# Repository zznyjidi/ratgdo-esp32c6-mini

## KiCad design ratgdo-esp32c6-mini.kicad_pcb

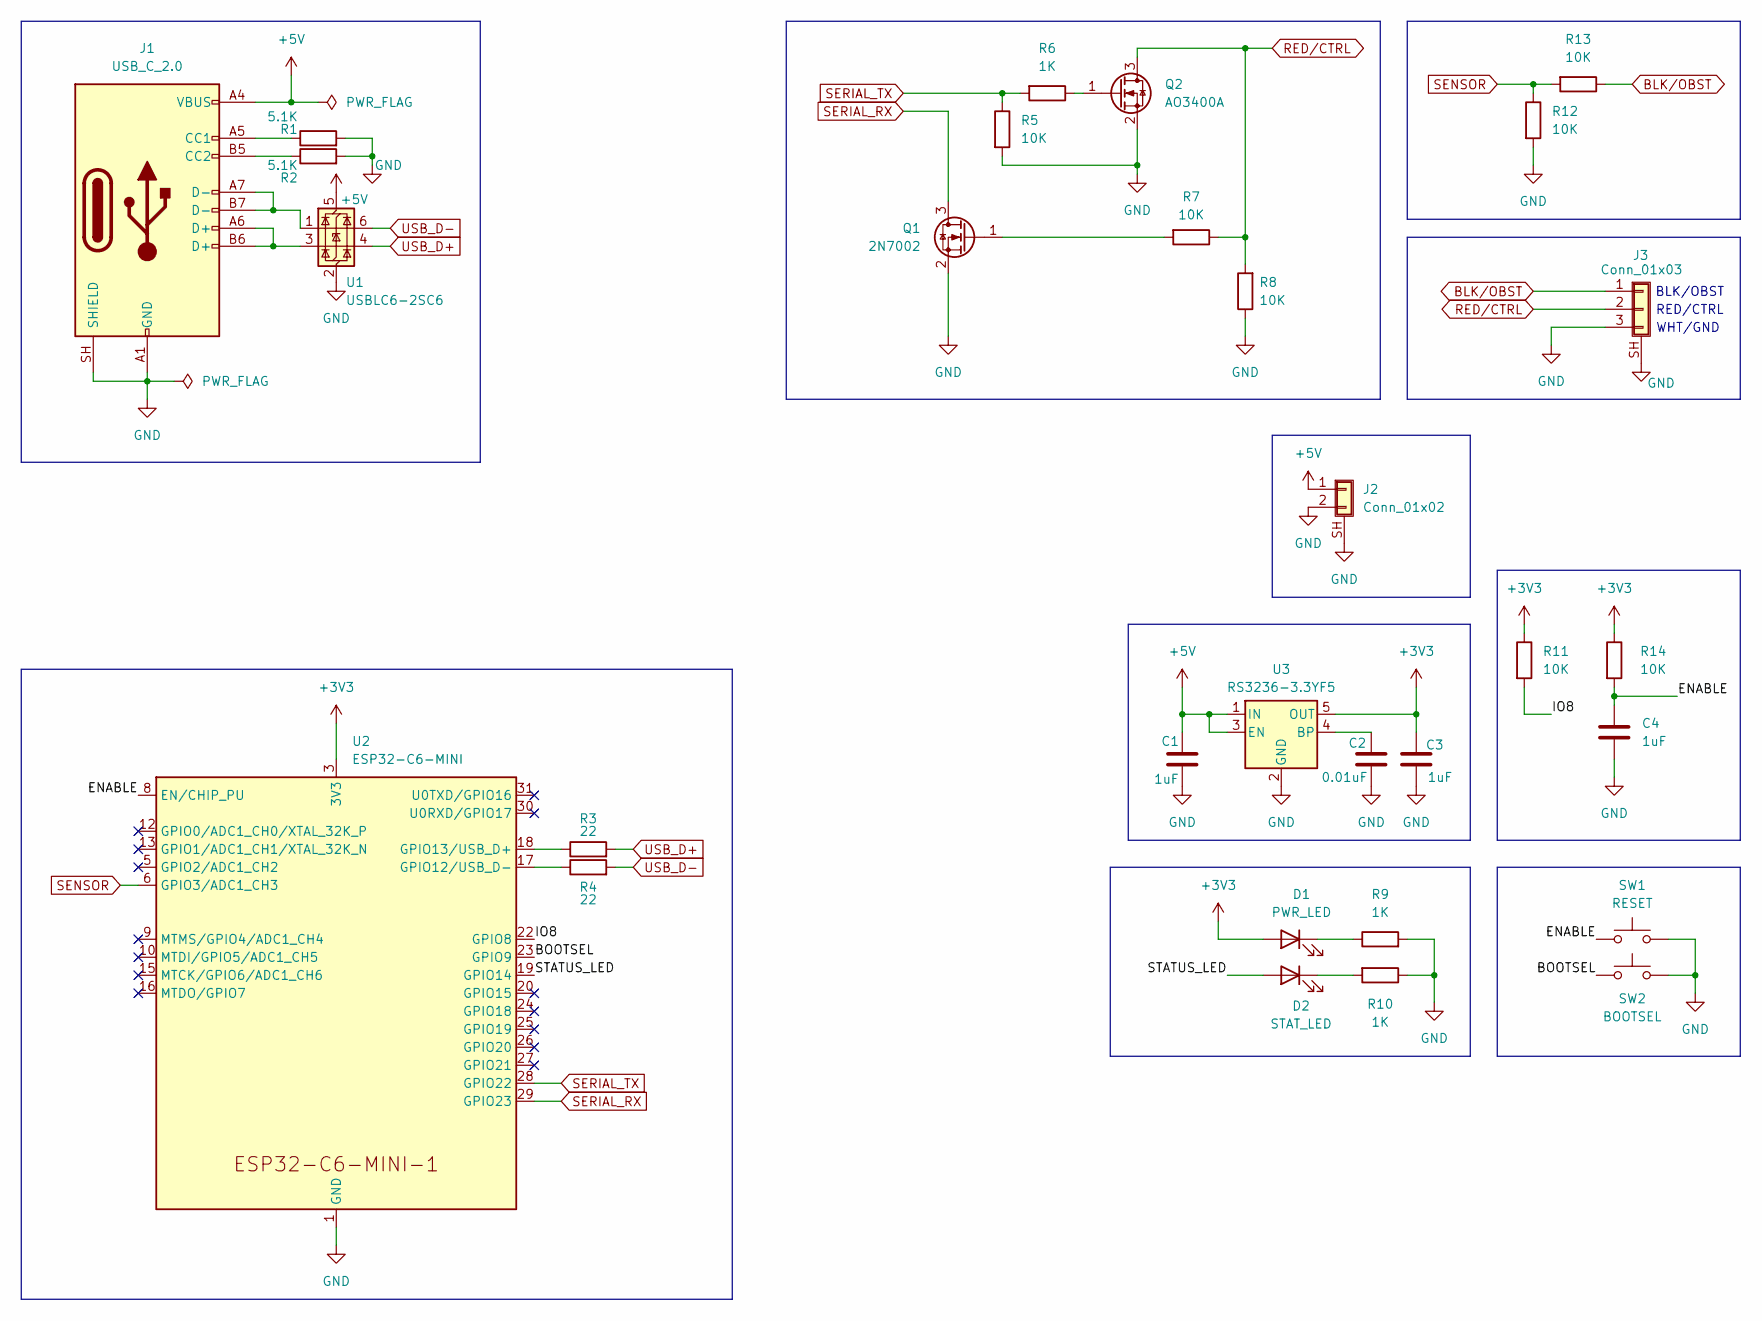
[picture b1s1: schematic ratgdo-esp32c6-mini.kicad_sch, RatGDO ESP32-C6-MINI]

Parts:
C1, C3, C4: 1uF; C_0402_1005Metric; LCSC PN C52923
C2: 0.01uF; C_0402_1005Metric; LCSC PN C15195
D1: PWR_LED; LED_0805_2012Metric; LCSC PN C84260
D2: STAT_LED; LED_0805_2012Metric; LCSC PN C84256
J1: USB_C_2.0; USB_C_Receptacle_G-Switch_GT-USB-7010ASV; LCSC PN C2765186
J2: Conn_01x02
J3: Conn_01x03
Q1: 2N7002; SOT-23; LCSC PN C81445
Q2: AO3400A; SOT-23; LCSC PN C347475
R1, R2: 5.1K; R_0402_1005Metric; LCSC PN C105872
R3, R4: 22; R_0402_1005Metric; LCSC PN C114765
R5, R7, R8, R12, R13: 10K; R_0402_1005Metric; LCSC# C17414
R6: 1K; R_0402_1005Metric; LCSC# C17513
R9, R10: 1K; R_0402_1005Metric; LCSC PN C106235
R11, R14: 10K; R_0402_1005Metric; LCSC PN C60490
SW1: RESET; SW_Push_SPST_NO_Alps_SKRK; LCSC PN C720477
SW2: BOOTSEL; SW_Push_SPST_NO_Alps_SKRK; LCSC PN C720477
U1: USBLC6-2SC6; SOT-23-6; LCSC PN C7519
U2: ESP32-C6-MINI; ESP32-C6-MINI-1; LCSC PN C5736265
U3: RS3236-3.3YF5; SOT-23-5; LCSC PN C379349

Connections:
+3V3: C3.1, D1.2 (A), R11.1, R14.1, U2.3 (3V3), U3.5 (OUT)
+5V: C1.1, J1.A4 (VBUS), J1.A9 (VBUS), J1.B4 (VBUS), J1.B9 (VBUS), J2.1, U1.5 (VBUS), U3.1 (IN), U3.3 (EN)
/BOOTSEL: SW2.1, U2.23 (GPIO9)
/ENABLE: C4.1, R14.2, SW1.1, U2.8 (EN/CHIP_PU)
/IO8: R11.2, U2.22 (GPIO8)
/STATUS_LED: D2.2 (A), U2.19 (GPIO14)
BLK/OBST: J3.1, R13.1
GND: C1.2, C2.2, C3.2, C4.2, J1.A1 (GND), J1.A12 (GND), J1.B1 (GND), J1.B12 (GND), J1.SH (SHIELD), J2.2, J2.3, J2.4, J2.SH (Shield), J3.3, J3.4, J3.5, J3.SH (Shield), Q1.2 (S), Q2.2 (S), R1.2, R2.2, R5.2, R8.1, R9.2, R10.1, R12.2, SW1.2, SW2.2, U1.2 (GND), U2.1 (GND), U2.2 (GND), U2.11 (GND), U2.14 (GND), U2.36 (GND), U2.37 (GND), U2.38 (GND), U2.39 (GND), U2.40 (GND), U2.41 (GND), U2.42 (GND), U2.43 (GND), U2.44 (GND), U2.45 (GND), U2.46 (GND), U2.47 (GND), U2.48 (GND), U2.49 (GND), U2.50 (GND), U2.51 (GND), U2.52 (GND), U2.53 (GND), U3.2 (GND)
unnamed: D1.1 (K), R9.1
unnamed: D2.1 (K), R10.2
unnamed: J1.A5 (CC1), R1.1
unnamed: J1.B5 (CC2), R2.1
unnamed: J1.A6 (D+), J1.B6 (D+), U1.3 (I/O2)
unnamed: J1.A7 (D-), J1.B7 (D-), U1.1 (I/O1)
unnamed: Q1.1 (G), R7.2
unnamed: Q2.1 (G), R6.1
unnamed: R4.1, U2.17 (GPIO12/USB_D-)
unnamed: R3.1, U2.18 (GPIO13/USB_D+)
unnamed: C2.1, U3.4 (BP)
RED/CTRL: J3.2, Q2.3 (D), R7.1, R8.2
SENSOR: R12.1, R13.2, U2.6 (GPIO3/ADC1_CH3)
SERIAL_RX: Q1.3 (D), U2.29 (GPIO23)
SERIAL_TX: R5.1, R6.2, U2.28 (GPIO22)
USB_D+: R3.2, U1.4 (I/O2)
USB_D-: R4.2, U1.6 (I/O1)

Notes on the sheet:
WHT/GND
RED/CTRL
BLK/OBST

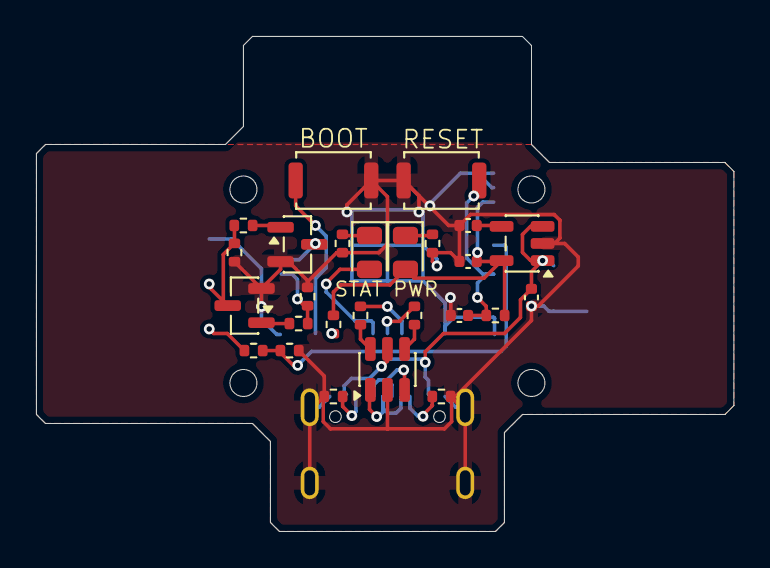
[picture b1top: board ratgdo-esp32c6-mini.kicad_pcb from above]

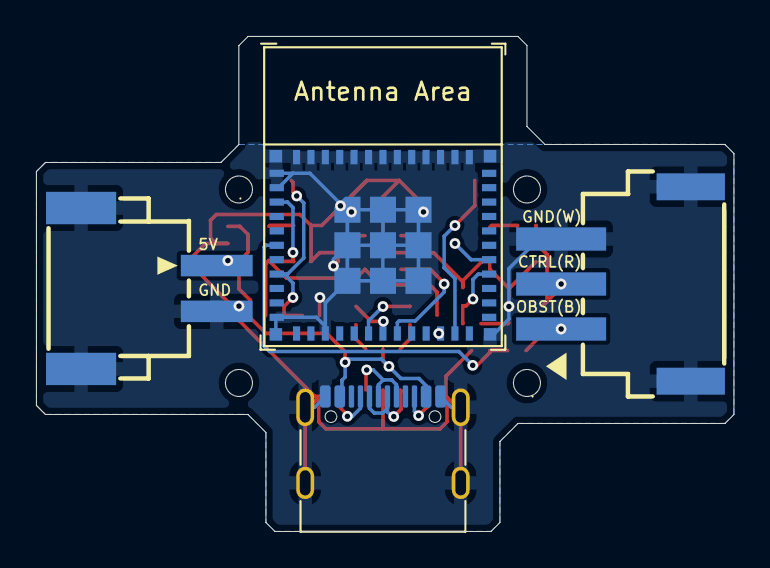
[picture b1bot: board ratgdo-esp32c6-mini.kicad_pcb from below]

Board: 2 copper layers, 38.8 x 27.5 mm, 30 parts (4 on the bottom side), 25 nets.

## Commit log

2026-06-06 base schematic with esp32c6-mini
2026-06-06 add footprint & LCSC PN
2026-06-06 add LCSC footprint
2026-06-06 replace screw terminal with connector
2026-06-06 add dedicated power input
2026-06-06 change R&C to 0402 size
2026-06-06 sync pcb with schematic
2026-06-08 layout components
2026-06-08 wiring
2026-06-08 edge
2026-06-08 wiring & cut
2026-06-08 add wire label
2026-06-08 add mounting hole
2026-06-08 remove warning marks
2026-06-10 move via
2026-06-10 add fabrication settings
